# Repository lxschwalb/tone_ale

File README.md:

# Tone Ale
Reprogrammable rp2040 based guitar pedal with capacitive touch sensing. Some effects are toggled on and off by tapping on the pedal surface, others act as expression pedals by increasing and decreasing the pressure/surface area you apply to the pedal.

## Effects:
* audio interface
  * 2 input 2 output usb audio interface. Tap on pedal surface to mute/unmute it. LED indicates mute status. Only 48kHz 32bit audio supported.
* cabinet simulator
  * Guitar cabinet simulator using an impulse response.
* delay
  * Stereo digital delay. Each repeat is half the volume of the previous. Set feedback to false for only one repeat. Change delay buffer size for a different delay time. set it to an odd number for ping pong delay.
* fuzz
  * Simple fuzz. Turn on the gate for a tight velcro sound. Change the gain and clipping levels to taste.
* low pass filter
  * Always on low pass filter. Cuttoff frequency is determined by pressure applied to pedal. When not touching the pedal the cuttoff frequency should be higher than audible range so it is as if there is no filter.
* phaser
  * phaser effect with various parameters that can be tuned in code.
* rig
  * fuzz and cabinet simulator together in one effect which kind of gives the sound of a full guitar rig.
* sample player (amen beat)
  * sample starts playing when you place your foot on the pedal and stops when you take it away. It restarts from the beginning everytime. Increasing and decreasing the pressure/surface area changes the volume.
* sample rate reducer
  * By default the sample rate is 48kH and there is no aliasing. By stepping on the pedal you decrease the sample rate and introduce aliasing artifacts. The harder you press the more the sample rate drops.
* unstable noise generator
  * Unstable IIR filter. It chaotically generates weird sounds which are effected by the input in unpredictable ways.
* vibrato
  * pitch shifting vibrato
* wah
  * classic band pass filter wah sound. It engages when you step on the pedal and then you control the wah using pressure. As soon as you remove your foot it outputs the dry signal again.
* wavefolder
  * Similar to fuzz, except instead of clipping it folds the part of the signal above the threshold back down.

## Where to get one?
Everything necesary to build your own Tone Ale is available on this repository, but if you want to buy a fully assembled Pedal send an email to toneagetechnology@gmail.com. Profits are donated to effective charities.

Pedals will be sold for CHF125. In spirit of full transparency, I will share that my production cost per pedal is between CHF20 and CHF30 depending on a few varying factors. It would likely cost you more. It's cheaper for me since I'm producing it in bulk and already have a lot of the tools required. I will assume it's a fixed CHF25 and donate CHF100 for every pedal sold. This production cost does not include my time/labour, because that is done pro bono.

For questions about my charity selection process, motivation for doing this, or if you have a prefered charity you want payment for your pedal donated to, you can also email toneagetechnology@gmail.com.

## Upload new effect
You don't need to be able to develop or install special software to upload new effects. All you need is a usb port, cable, and something conductive (a piece of tin foil will to).

To upload new effects, connect the pedal to a computer with a usb cable, touch the part of the pcb shown in the image below with a piece of tin foil and drag it to the side as shown. Now the pedal shows up as a mass storage device. Just drag and drop the uf2 file(found in /compiled_effects) of the corresponding effect and you're all set to go.

## Compile effects
Perhaps you want to alter some effects before uploading it onto the pedal. For example you might want to increase the gain of the fuzz. This would require recompiling the effect after the changes to the code have been made. Follow the steps below to recompile:

First set up the Pi Pico SDK according to [this guide](https://www.raspberrypi.com/documentation/microcontrollers/c_sdk.html#sdk-setup)

Open terminal in the main project folder (called tone_ale) and run the following commands:

`cp <pico_sdk_path>/external/pico_sdk_import.cmake .` (replace <pico_sdk_path> with wherever you set up the SDK)

`cd /build`

`cmake ..`

`make`

This will compile each effect and place it in "/build/<effect_name>/<effect_name>.uf2". This uf2 file can then directly be uploaded onto the pedal using the method descibed above

## Develop new effects
TODO explain this

## Pinout
The pinout is shown below.
* POT0, POT1, POT2 and POT3 can be programmed as analog inputs, so they can be used for adding potentiometers (knobs)
* GP0, GP1, GP2, GP3, GP4, GP5 and GP6 are general purpose digital input/output pins, so they can be used for many different things including LEDs, buttons, digitally communicating with external devices such as displays etc.
* If you want to chain multiple Tone Ale's together, you can reduce cost and improve fidelity by not putting DACs and ADCs between them and just directly connect their VBUS, GND, I2CV_CLK, I2CV_WS and connect the I2CV_OUT from the first pedal to the I2CV_IN of the second. You can chain many pedals together in this way (it's been tested up to 4). NB: Only the first pedal in the chain should have an PCM1808 soldered on, otherwise the I2CV_CLK and I2CV_WS will be driven by multiple sources. Alternatively you can run a different firmware on all pedals except the first one in the chain where the PCM1808 does not generate a clock. (TODO: explain how to do this)

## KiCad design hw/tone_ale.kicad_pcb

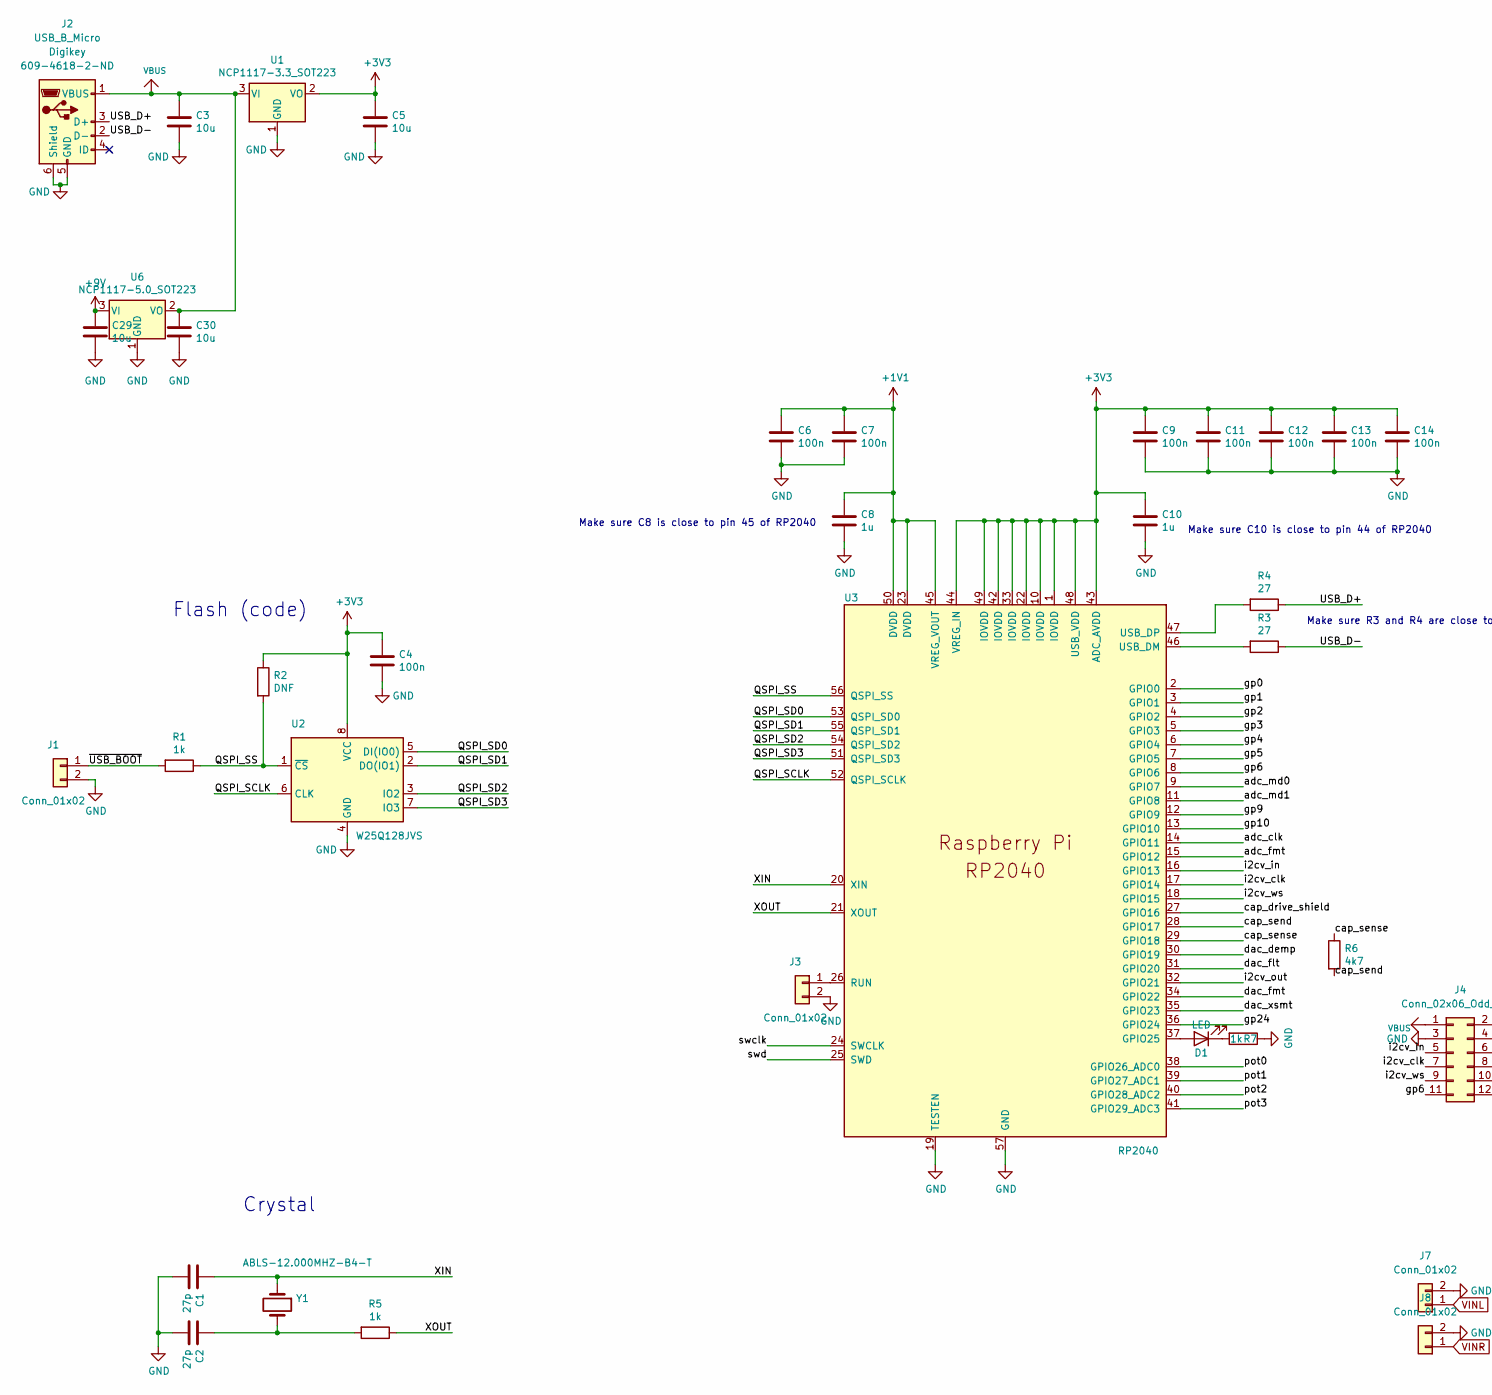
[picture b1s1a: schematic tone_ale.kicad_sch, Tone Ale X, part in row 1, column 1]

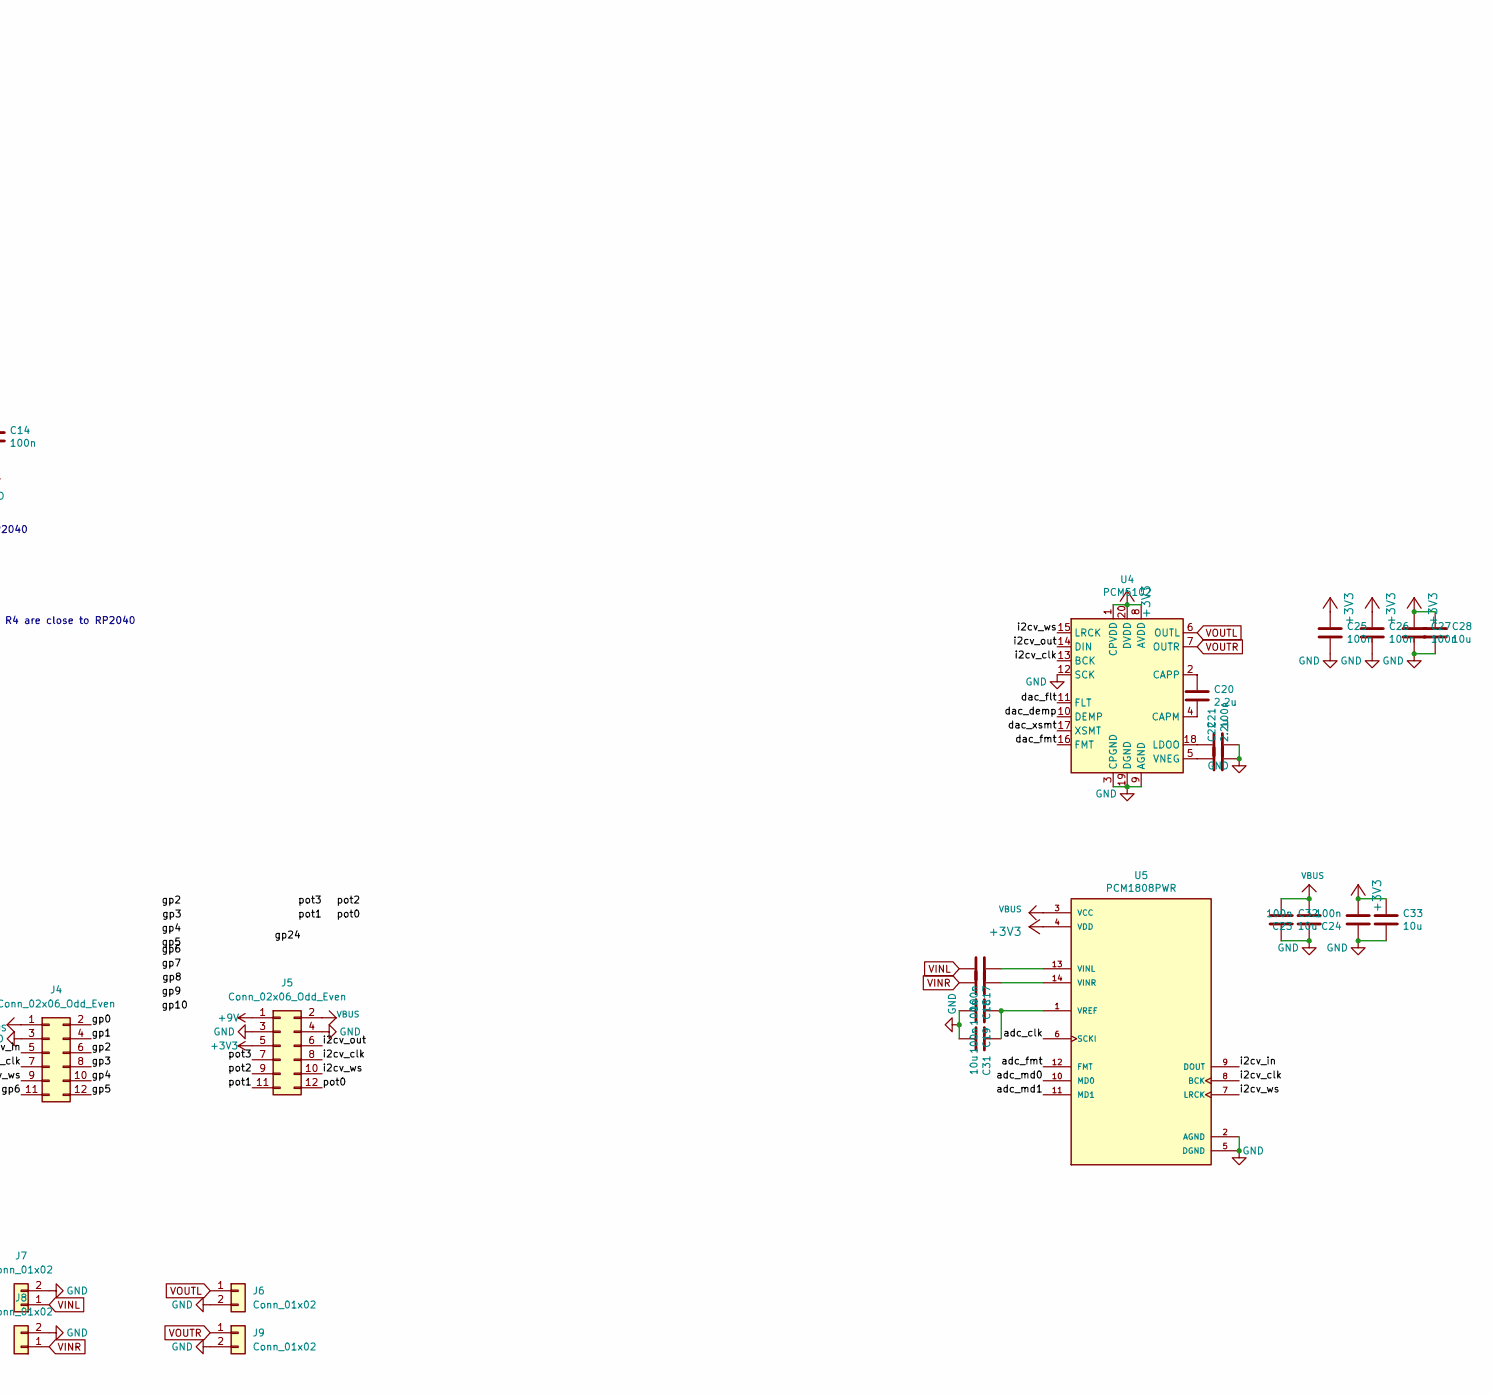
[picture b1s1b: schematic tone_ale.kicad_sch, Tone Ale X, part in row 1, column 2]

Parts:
C1, C2: 27p; C_0402_1005Metric
C3, C5, C29, C30: 10u; C_0805_2012Metric
C4, C6, C7, C9, C11, C12, C13, C14, C17, C18, C19, C21, C23, C24, C25, C26, C27: 100n; C_0402_1005Metric
C8, C10: 1u; C_0402_1005Metric
C20, C22: 2.2u; C_0402_1005Metric
C28, C31, C32, C33: 10u; CP_Radial_D4.0mm_P1.50mm
D1: LED; LED_D3.0mm_Horizontal_O1.27mm_Z2.0mm
J1, J3: Conn_01x02; SolderJumper-2_P1.3mm_Open_TrianglePad1.0x1.5mm
J2: USB_B_Micro; USB_Micro-B_Amphenol_10104110_Horizontal
J4, J5: Conn_02x06_Odd_Even; PinHeader_2x06_P2.54mm_Vertical
J6, J7, J8, J9: Conn_01x02; acjm_mhdr
R1, R5, R7: 1k; C_0402_1005Metric
R2: DNF; C_0402_1005Metric
R3, R4: 27; C_0402_1005Metric
R6: 4k7; C_0402_1005Metric
U1: NCP1117-3.3_SOT223; SOT-223-3_TabPin2
U2: W25Q128JVS; SOIC-8_5.23x5.23mm_P1.27mm; Part Nr W25Q128JVSIMTR (digikey)
U3: RP2040; RP2040-QFN-56; Part Nr 2648-SC0914(13)TR-ND
U4: PCM5102; TSSOP-20_4.4x6.5mm_P0.65mm
U5: PCM1808PWR; SOP65P640X120-14N; PARTREV B
U6: NCP1117-5.0_SOT223; SOT-223-3_TabPin2
Y1: ABLS-12.000MHZ-B4-T; ABLS_crystal_12.7x04.7; Part Nr 535-10218-2-ND (digikey)

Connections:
+1V1: C6.1, C7.1, C8.1, U3.23 (DVDD), U3.45 (VREG_VOUT), U3.50 (DVDD)
+3V3: C4.1, C5.1, C9.1, C10.1, C11.1, C12.1, C13.1, C14.1, C24.2, C25.1, C26.1, C27.1, C28.1, C33.1, J5.5, R2.1, U1.2 (VO), U2.8 (VCC), U3.1 (IOVDD), U3.10 (IOVDD), U3.22 (IOVDD), U3.33 (IOVDD), U3.42 (IOVDD), U3.43 (ADC_AVDD), U3.44 (VREG_IN), U3.48 (USB_VDD), U3.49 (IOVDD), U4.1 (CPVDD), U4.8 (AVDD), U4.20 (DVDD), U5.4 (VDD)
+9V: C29.1, J5.1, U6.3 (VI)
/QSPI_SCLK: U2.6 (CLK), U3.52 (QSPI_SCLK)
/QSPI_SD0: U2.5 (DI(IO0)), U3.53 (QSPI_SD0)
/QSPI_SD1: U2.2 (DO(IO1)), U3.55 (QSPI_SD1)
/QSPI_SD2: U2.3 (IO2), U3.54 (QSPI_SD2)
/QSPI_SD3: U2.7 (IO3), U3.51 (QSPI_SD3)
/QSPI_SS: R1.1, R2.2, U2.1 (~CS), U3.56 (QSPI_SS)
/USB_D+: J2.3 (D+), R4.1
/USB_D-: J2.2 (D-), R3.1
/XIN: C1.1, U3.20 (XIN), Y1.1
/XOUT: R5.1, U3.21 (XOUT)
/adc_clk: U3.14 (GPIO11), U5.6 (SCKI)
/adc_fmt: U3.15 (GPIO12), U5.12 (FMT)
/adc_md0: U3.9 (GPIO7), U5.10 (MD0)
/adc_md1: U3.11 (GPIO8), U5.11 (MD1)
/cap_drive_shield: U3.27 (GPIO16)
/cap_send: R6.2, U3.28 (GPIO17)
/cap_sense: R6.1, U3.29 (GPIO18)
/dac_demp: U3.30 (GPIO19), U4.10 (DEMP)
/dac_flt: U3.31 (GPIO20), U4.11 (FLT)
/dac_fmt: U3.34 (GPIO22), U4.16 (FMT)
/dac_xsmt: U3.35 (GPIO23), U4.17 (XSMT)
/gp0: J4.2, U3.2 (GPIO0)
/gp1: J4.4, U3.3 (GPIO1)
/gp2: J4.6, U3.4 (GPIO2)
/gp3: J4.8, U3.5 (GPIO3)
/gp4: J4.10, U3.6 (GPIO4)
/gp5: J4.12, U3.7 (GPIO5)
/gp6: J4.11, U3.8 (GPIO6)
/gp9: U3.12 (GPIO9)
/gp10: U3.13 (GPIO10)
/gp24: U3.36 (GPIO24)
/i2cv_clk: J4.7, J5.8, U3.17 (GPIO14), U4.13 (BCK), U5.8 (BCK)
/i2cv_in: J4.5, U3.16 (GPIO13), U5.9 (DOUT)
/i2cv_out: J5.6, U3.32 (GPIO21), U4.14 (DIN)
/i2cv_ws: J4.9, J5.10, U3.18 (GPIO15), U4.15 (LRCK), U5.7 (LRCK)
/pot0: J5.12, U3.38 (GPIO26_ADC0)
/pot1: J5.11, U3.39 (GPIO27_ADC1)
/pot2: J5.9, U3.40 (GPIO28_ADC2)
/pot3: J5.7, U3.41 (GPIO29_ADC3)
/swclk: U3.24 (SWCLK)
/swd: U3.25 (SWD)
/~USB_BOOT: J1.1, R1.2
GND: C1.2, C2.2, C3.2, C4.2, C5.2, C6.2, C7.2, C8.2, C9.2, C10.2, C11.2, C12.2, C13.2, C14.2, C19.2, C21.2, C22.2, C23.1, C24.1, C25.2, C26.2, C27.2, C28.2, C29.2, C30.2, C31.2, C32.2, C33.2, J1.2, J2.5 (GND), J2.6 (Shield), J3.2, J4.3, J5.3, J5.4, J6.2, J7.2, J8.2, J9.2, R7.1, U1.1 (GND), U2.4 (GND), U3.19 (TESTEN), U3.57 (GND), U4.3 (CPGND), U4.9 (AGND), U4.12 (SCK), U4.19 (DGND), U5.2 (AGND), U5.5 (DGND), U6.1 (GND)
unnamed: C2.1, R5.2, Y1.2
unnamed: C17.1, U5.13 (VINL)
unnamed: C18.1, U5.14 (VINR)
unnamed: C19.1, C31.1, U5.1 (VREF)
unnamed: C20.1, U4.2 (CAPP)
unnamed: C20.2, U4.4 (CAPM)
unnamed: C21.1, U4.18 (LDOO)
unnamed: C22.1, U4.5 (VNEG)
unnamed: D1.1 (K), R7.2
unnamed: D1.2 (A), U3.37 (GPIO25)
unnamed: J3.1, U3.26 (RUN)
unnamed: R3.2, U3.46 (USB_DM)
unnamed: R4.2, U3.47 (USB_DP)
VBUS: C3.1, C23.2, C30.1, C32.1, J2.1 (VBUS), J4.1, J5.2, U1.3 (VI), U5.3 (VCC), U6.2 (VO)
VINL: C17.2, J7.1
VINR: C18.2, J8.1
VOUTL: J6.1, U4.6 (OUTL)
VOUTR: J9.1, U4.7 (OUTR)

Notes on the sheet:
Flash (code)
Make sure R3 and R4 are close to RP2040
Crystal
Make sure C10 is close to pin 44 of RP2040
Make sure C8 is close to pin 45 of RP2040

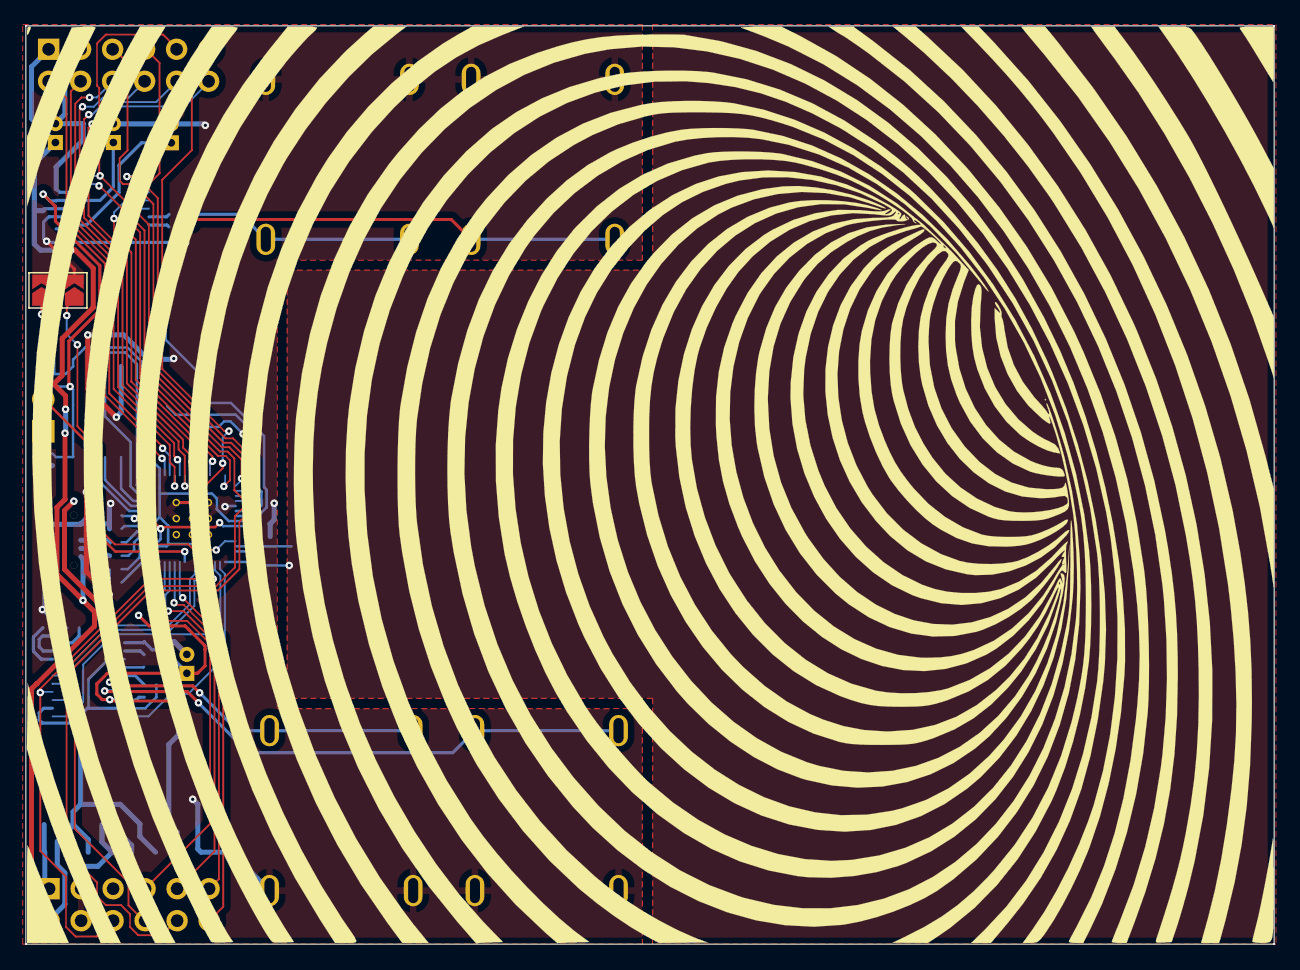
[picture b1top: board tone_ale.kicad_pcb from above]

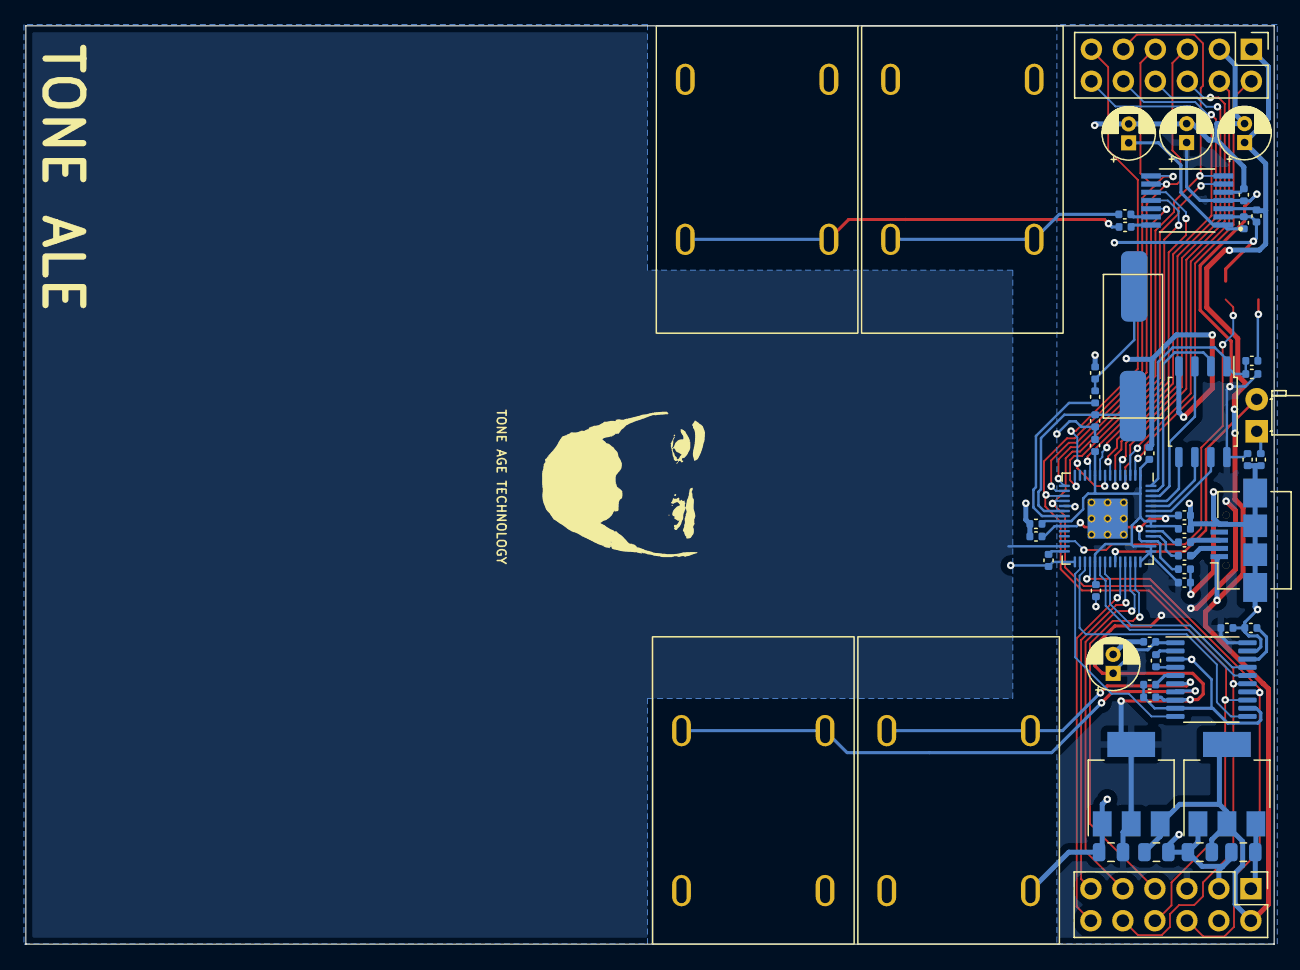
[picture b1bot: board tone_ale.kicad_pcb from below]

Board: 2 copper layers, 99.1 x 72.9 mm, 55 parts (53 on the bottom side), 58 nets.

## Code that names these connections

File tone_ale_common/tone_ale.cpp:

/**
 * Copyright (c) 2022 Tone Age Technology
 *
 * SPDX-License-Identifier: BSD-3-Clause
 */

#include <stdio.h>
#include "pico/stdlib.h"

#define LED_PIN         25
#define ADC_FMT_PIN     12
#define ADC_MD0_PIN     7
#define ADC_MD1_PIN     8
#define DAC_DEMP_PIN    19
#define DAC_FLT_PIN     20
#define DAC_FMT_PIN     22
#define DAC_XSMT_PIN    23


#define __24bitmax__    (8388000/2)
#define __24bitmin__    (-8388000/2)

void tone_ale_pins_setup() {
    gpio_init(LED_PIN);
    gpio_init(ADC_FMT_PIN);
    gpio_init(ADC_MD0_PIN);
    gpio_init(ADC_MD1_PIN);
    gpio_init(DAC_DEMP_PIN);
    gpio_init(DAC_FLT_PIN);
    gpio_init(DAC_FMT_PIN);
    gpio_init(DAC_XSMT_PIN);

    gpio_set_dir(LED_PIN, GPIO_OUT);
    gpio_set_dir(ADC_FMT_PIN, GPIO_OUT);
    gpio_set_dir(ADC_MD0_PIN, GPIO_OUT);
    gpio_set_dir(ADC_MD1_PIN, GPIO_OUT);
    gpio_set_dir(DAC_DEMP_PIN, GPIO_OUT);
    gpio_set_dir(DAC_FLT_PIN, GPIO_OUT);
    gpio_set_dir(DAC_FMT_PIN, GPIO_OUT);
    gpio_set_dir(DAC_XSMT_PIN, GPIO_OUT);

    gpio_put(LED_PIN, 1);
    gpio_put(ADC_FMT_PIN, 0);
    gpio_put(ADC_MD0_PIN, 1);
    gpio_put(ADC_MD1_PIN, 1);
    gpio_put(DAC_DEMP_PIN, 0);
    gpio_put(DAC_FLT_PIN, 1);
    gpio_put(DAC_FMT_PIN, 0);
    gpio_put(DAC_XSMT_PIN, 1);
}

void set_led(bool state){
    gpio_put(LED_PIN, state);
}

bool get_led(){
    return gpio_get(LED_PIN);
}

int32_t clip_shift(int32_t x) {
    // *256 rather than <<8 because left-shifting negative values is undefined behaviour
    if(x>__24bitmax__) {return __24bitmax__*256;}
    if(x<__24bitmin__) {return __24bitmin__*256;}
    else {return x*256;}
}

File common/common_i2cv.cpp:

/**
 * Copyright (c) 2023 Tone Age Technology
 *
 * SPDX-License-Identifier: BSD-3-Clause
 */
#include "hardware/dma.h"
#include "hardware/irq.h"
#include "hardware/pio.h"
#include "i2cv.pio.h"

#define ADC_CLK_PIN         11
#define CLK_PIN             14
#define WS_PIN              15
#define I2CV_OUT_PIN        21
#define I2CV_IN_PIN         13

static int32_t *i2cv_tx_buff_ptr;
static int32_t *i2cv_rx_buff_ptr;
static int32_t *i2cv_x_buff_ptr;
static int32_t *i2cv_temp_ptr;

static int dma_out_chan = dma_claim_unused_channel(true);
static int dma_in_chan = dma_claim_unused_channel(true);

void juggle_buffers() { // TODO align left and right channels
    dma_hw->ints0 = 1u << dma_out_chan;

	i2cv_temp_ptr = i2cv_tx_buff_ptr;
	i2cv_tx_buff_ptr = i2cv_x_buff_ptr;
	i2cv_x_buff_ptr = i2cv_rx_buff_ptr;
	i2cv_rx_buff_ptr = i2cv_temp_ptr;
    
    dma_channel_set_read_addr(dma_out_chan, i2cv_tx_buff_ptr, true);
    dma_channel_set_write_addr(dma_in_chan, i2cv_rx_buff_ptr, true);
}

void common_clk_setup(float samplerate, float system_clk) {
    float freq_div = system_clk/(4*24*samplerate);
    uint i2cv_clk_offset = pio_add_program(pio0, &i2cv_clocks_program);

    // Set up state machine that drives CLK and WS pins with appropriate frequencies
    uint i2cv_clk_sm = pio_claim_unused_sm(pio0, true);
    i2cv_clocks_program_init(pio0, i2cv_clk_sm, i2cv_clk_offset, CLK_PIN, WS_PIN);
    pio_sm_set_clkdiv(pio0, i2cv_clk_sm, freq_div);
    i2cv_clocks_set_ws_widths(pio0, i2cv_clk_sm, 24, 24);
    pio_sm_set_enabled(pio0, i2cv_clk_sm, true);

    // PCM1808 requires external clock, reuse i2cv_clocks state machine to generate it
    uint adc_clk_sm = pio_claim_unused_sm(pio0, true);
    i2cv_clocks_program_init(pio0, adc_clk_sm, i2cv_clk_offset, ADC_CLK_PIN, 10); //TODO remove magic number
    pio_sm_set_clkdiv(pio0, adc_clk_sm, freq_div/8);
    pio_sm_set_enabled(pio0, adc_clk_sm, true);
}

void common_i2cv_setup(int32_t *buff, int buffsize, void interrupt_service_routine()) {
    i2cv_tx_buff_ptr = buff;
    i2cv_rx_buff_ptr = &buff[buffsize];
    i2cv_x_buff_ptr = &buff[buffsize*2];

    // Set up state machine to send I2CV data in and out
    uint i2cv_offset = pio_add_program(pio0, &i2cv_bidirectional_program);
    uint i2cv_sm = pio_claim_unused_sm(pio0, true);
    i2cv_bidirectional_program_init(pio0, i2cv_sm, i2cv_offset, I2CV_OUT_PIN, WS_PIN, I2CV_IN_PIN);
    pio_sm_set_enabled(pio0, i2cv_sm, true);

    // Set up DMA for efficient transfers of buffers
    dma_channel_config c = dma_channel_get_default_config(dma_out_chan);
    channel_config_set_transfer_data_size(&c, DMA_SIZE_32);
    channel_config_set_read_increment(&c, true);
    channel_config_set_write_increment(&c, false);
    channel_config_set_dreq(&c, pio_get_dreq(pio0, i2cv_sm, true));

    dma_channel_config c_in = dma_channel_get_default_config(dma_in_chan);
    channel_config_set_transfer_data_size(&c_in, DMA_SIZE_32);
    channel_config_set_read_increment(&c_in, false);
    channel_config_set_write_increment(&c_in, true);
    channel_config_set_dreq(&c_in, pio_get_dreq(pio0, i2cv_sm, false));

    dma_channel_configure(
        dma_out_chan,
        &c,
        &pio0_hw->txf[i2cv_sm],
        i2cv_tx_buff_ptr,
        buffsize,
        false
    );

    dma_channel_configure(
        dma_in_chan,
        &c_in,
        i2cv_rx_buff_ptr,
        &pio0_hw->rxf[i2cv_sm],
        buffsize,
        false
    );

    // // Tell the DMA to raise IRQ line 0 when the channel finishes a block
    dma_channel_set_irq0_enabled(dma_out_chan, true);

    // // Configure the processor to run interrupt_service_routine() when DMA IRQ 0 is asserted
    irq_set_exclusive_handler(DMA_IRQ_0, interrupt_service_routine);
    irq_set_enabled(DMA_IRQ_0, true);

    // Manually call the handler once, to trigger the first transfer
    interrupt_service_routine();
}

int32_t * mutable_data() {
    return i2cv_x_buff_ptr;
}

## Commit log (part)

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2023-01-27 did stuff
2023-01-28 added effects
2023-01-30 added cab_sim and first version of rig
2023-01-30 I'm a dumb idiot who forgot to add CMakeLists.txt in the previous commit
2023-02-18 added usb audio interface functionality
2023-03-02 improved audio interface
2023-03-12 added samplerate_reducer and associated functionality to capsense
2023-03-19 renamed common stuff to tone ale stuff
2023-03-19 moved usb audio common stuff to its own file so that it's not included and recompiled in all the effects that do not use it. Added some other useful common functions
2023-03-21 Added Vibrato
2023-03-25 added phaser
2023-04-04 Added wah, lowpass, unstable as well as some other minor improvements
2023-04-05 added pics
2023-06-09 Updated hardware. Made wah only engaged while foot is on pedal
2023-06-09 added pic
2023-06-10 Accidentally swapped 2 sides
2023-06-10 Fixed channel alignment to be more robust and deterministic
2023-06-12 Fixed delay and added amen_beat
2023-06-12 forgot to add in previous commit
2023-06-25 Made the PCM1808 generate the clk and ws instead of the rp2040. Moved to use 32bit instead of 24bit audio as a default
2023-06-25 rename
2023-07-02 added line selector and made cab sim toggleable
2023-07-14 Made capacitive sensor self calibrate. Added compiled effects
2023-07-16 Improved Audio interface output
2023-07-16 Forgot to add uf2 file in previous commit
